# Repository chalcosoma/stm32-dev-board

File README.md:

# STM32 dev board

STM32 dev board

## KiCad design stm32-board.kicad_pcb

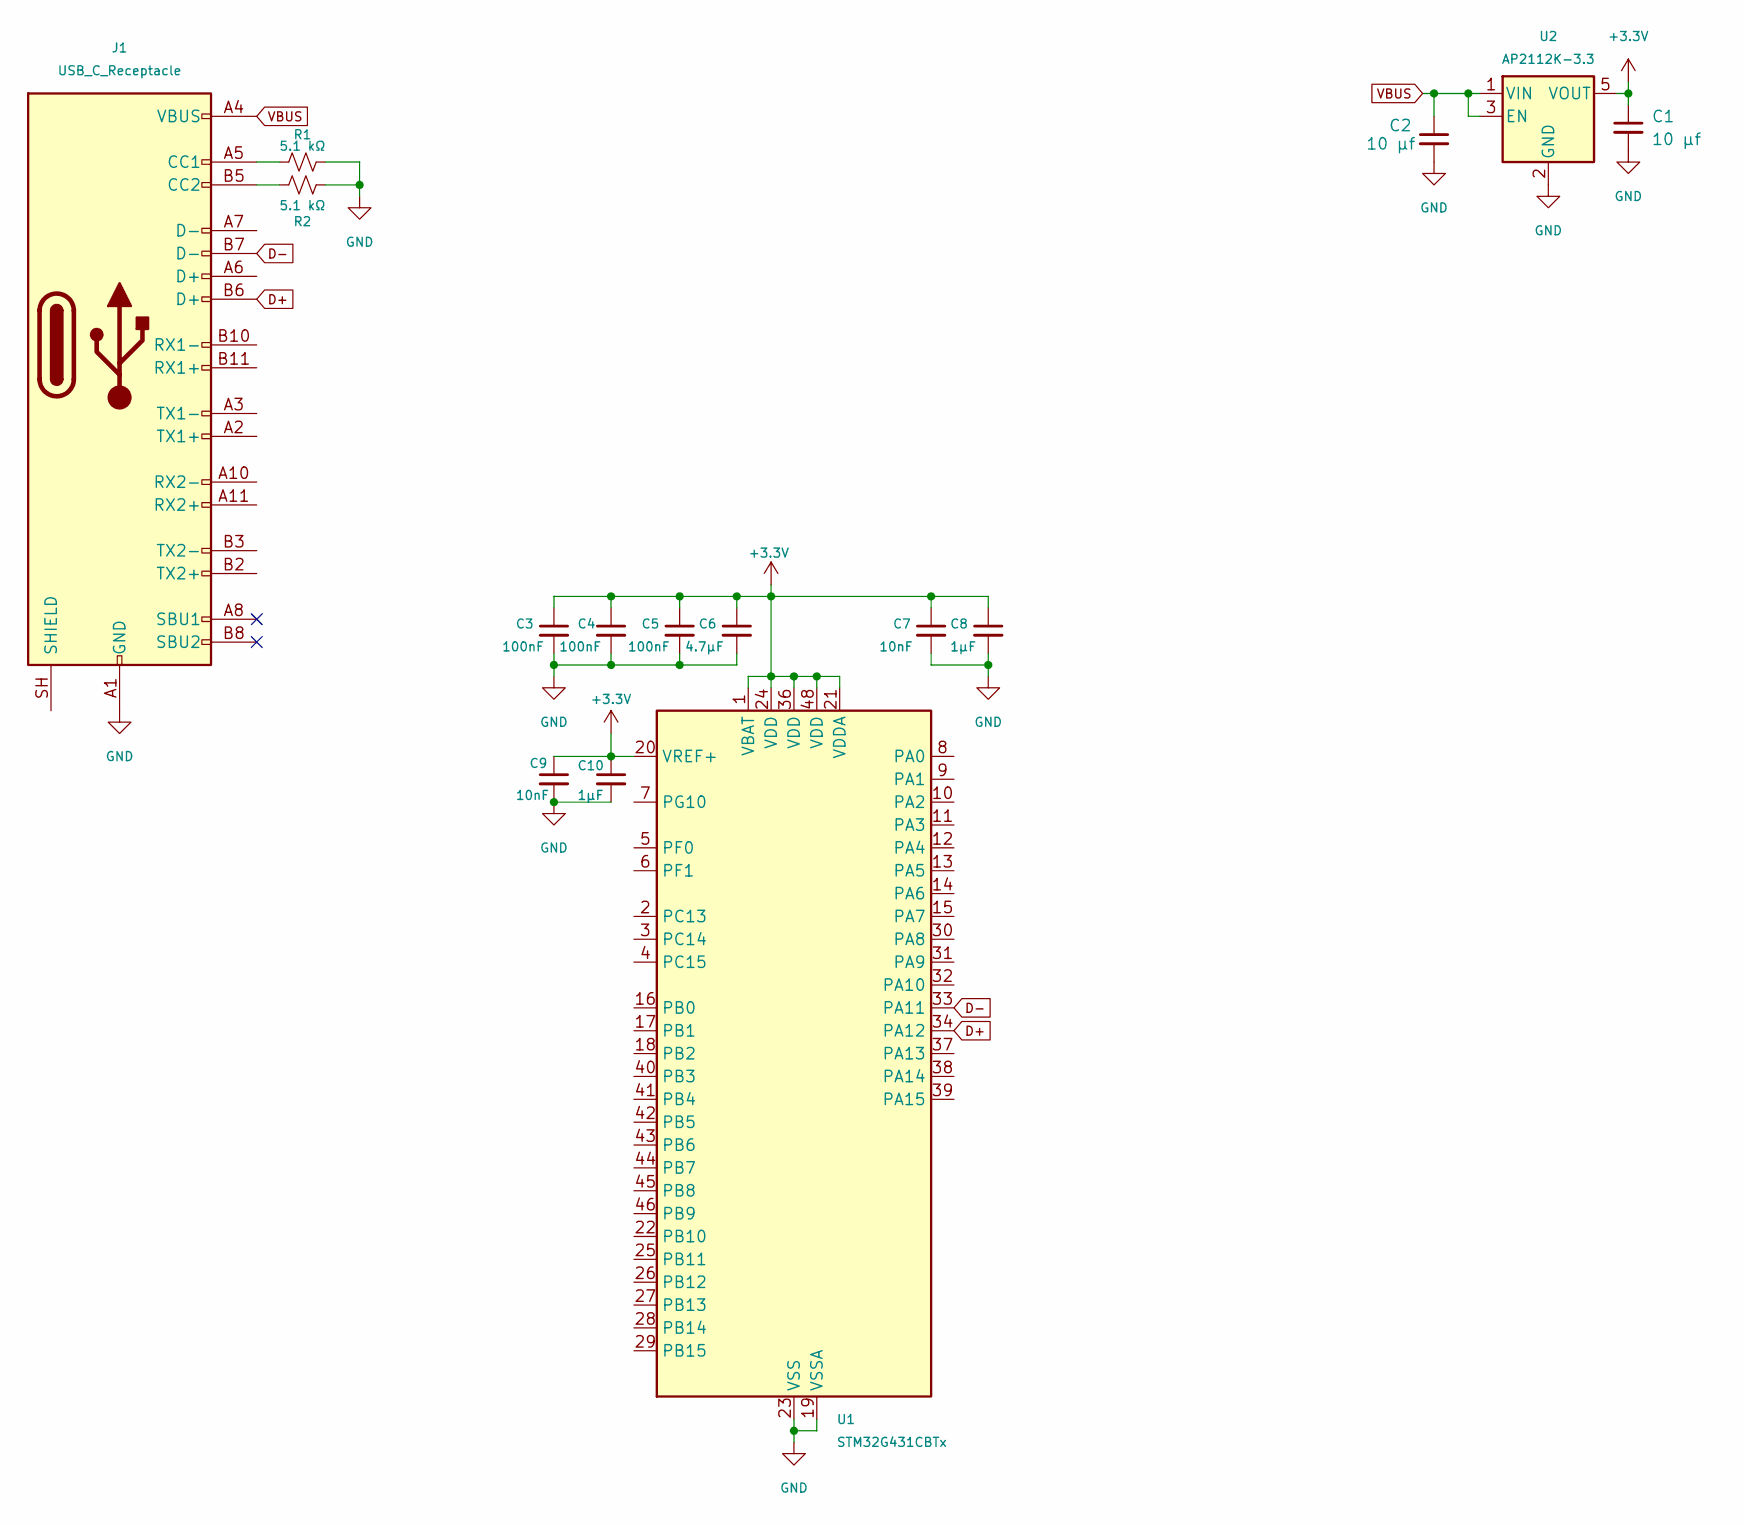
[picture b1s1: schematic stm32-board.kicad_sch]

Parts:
C1, C2: 10 µf; C_0603_1608Metric_Pad1.08x0.95mm_HandSolder
C3, C4, C5: 100nF; C_0603_1608Metric_Pad1.08x0.95mm_HandSolder
C6: 4.7µF; C_0603_1608Metric_Pad1.08x0.95mm_HandSolder
C7, C9: 10nF; C_0603_1608Metric_Pad1.08x0.95mm_HandSolder
C8, C10: 1µF; C_0603_1608Metric_Pad1.08x0.95mm_HandSolder
J1: USB_C_Receptacle; USB_C_Receptacle_Molex_105450-0101
R1, R2: 5.1 kΩ; R_0603_1608Metric_Pad0.98x0.95mm_HandSolder
U1: STM32G431CBTx; LQFP-48_7x7mm_P0.5mm
U2: AP2112K-3.3; SOT-23-5

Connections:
+3.3V: C1.1, C3.1, C4.1, C5.1, C6.1, C7.1, C8.1, C9.1, C10.1, U1.1 (VBAT), U1.20 (VREF+), U1.21 (VDDA), U1.24 (VDD), U1.36 (VDD), U1.48 (VDD), U2.5 (VOUT)
D+: J1.B6 (D+), U1.34 (PA12)
D-: J1.B7 (D-), U1.33 (PA11)
GND: C1.2, C2.2, C3.2, C4.2, C5.2, C6.2, C7.2, C8.2, C9.2, C10.2, J1.A1 (GND), J1.A12 (GND), J1.B1 (GND), J1.B12 (GND), R1.2, R2.1, U1.19 (VSSA), U1.23 (VSS), U1.35 (VSS), U1.47 (VSS), U2.2 (GND)
unnamed: J1.A5 (CC1), R1.1
unnamed: J1.B5 (CC2), R2.2
VBUS: C2.1, J1.A4 (VBUS), J1.A9 (VBUS), J1.B4 (VBUS), J1.B9 (VBUS), U2.1 (VIN), U2.3 (EN)

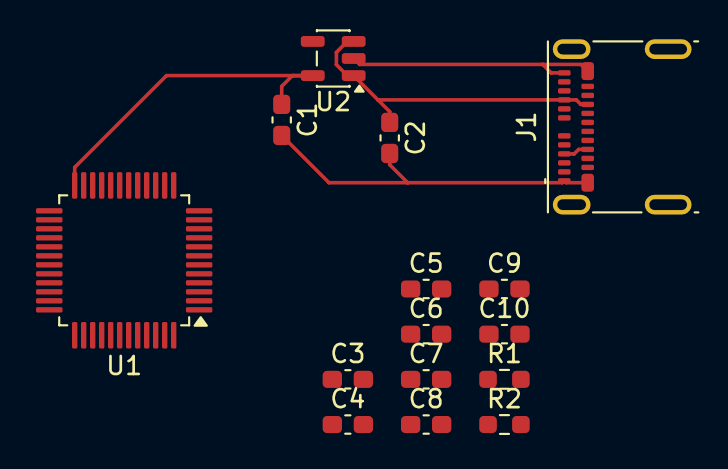
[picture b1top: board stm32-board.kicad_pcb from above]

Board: 2 copper layers, 15 parts (0 on the bottom side), 7 nets.
